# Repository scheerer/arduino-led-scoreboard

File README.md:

# Arduino LED Scoreboard

This project is intended to provide a simple arduino scoreboard based on the hub75 16x32 multi color LED (Example: [Adafruit - Medium 16x32 RGB LED matrix panel](https://www.adafruit.com/products/420)) and momentary RF receiver (Example: [Adafruit - Simple RF M4 315MHz](https://www.adafruit.com/products/1096))

# RF Receiver

Intended to be plugged directing into pins 2 thru 7 with the GND on pin 2

# LED Display

Wire as described in Adafruit's documentation for Arduino MEGA [LED Wiring Instructions](https://learn.adafruit.com/32x16-32x32-rgb-led-matrix/)

Feel free to ask questions...

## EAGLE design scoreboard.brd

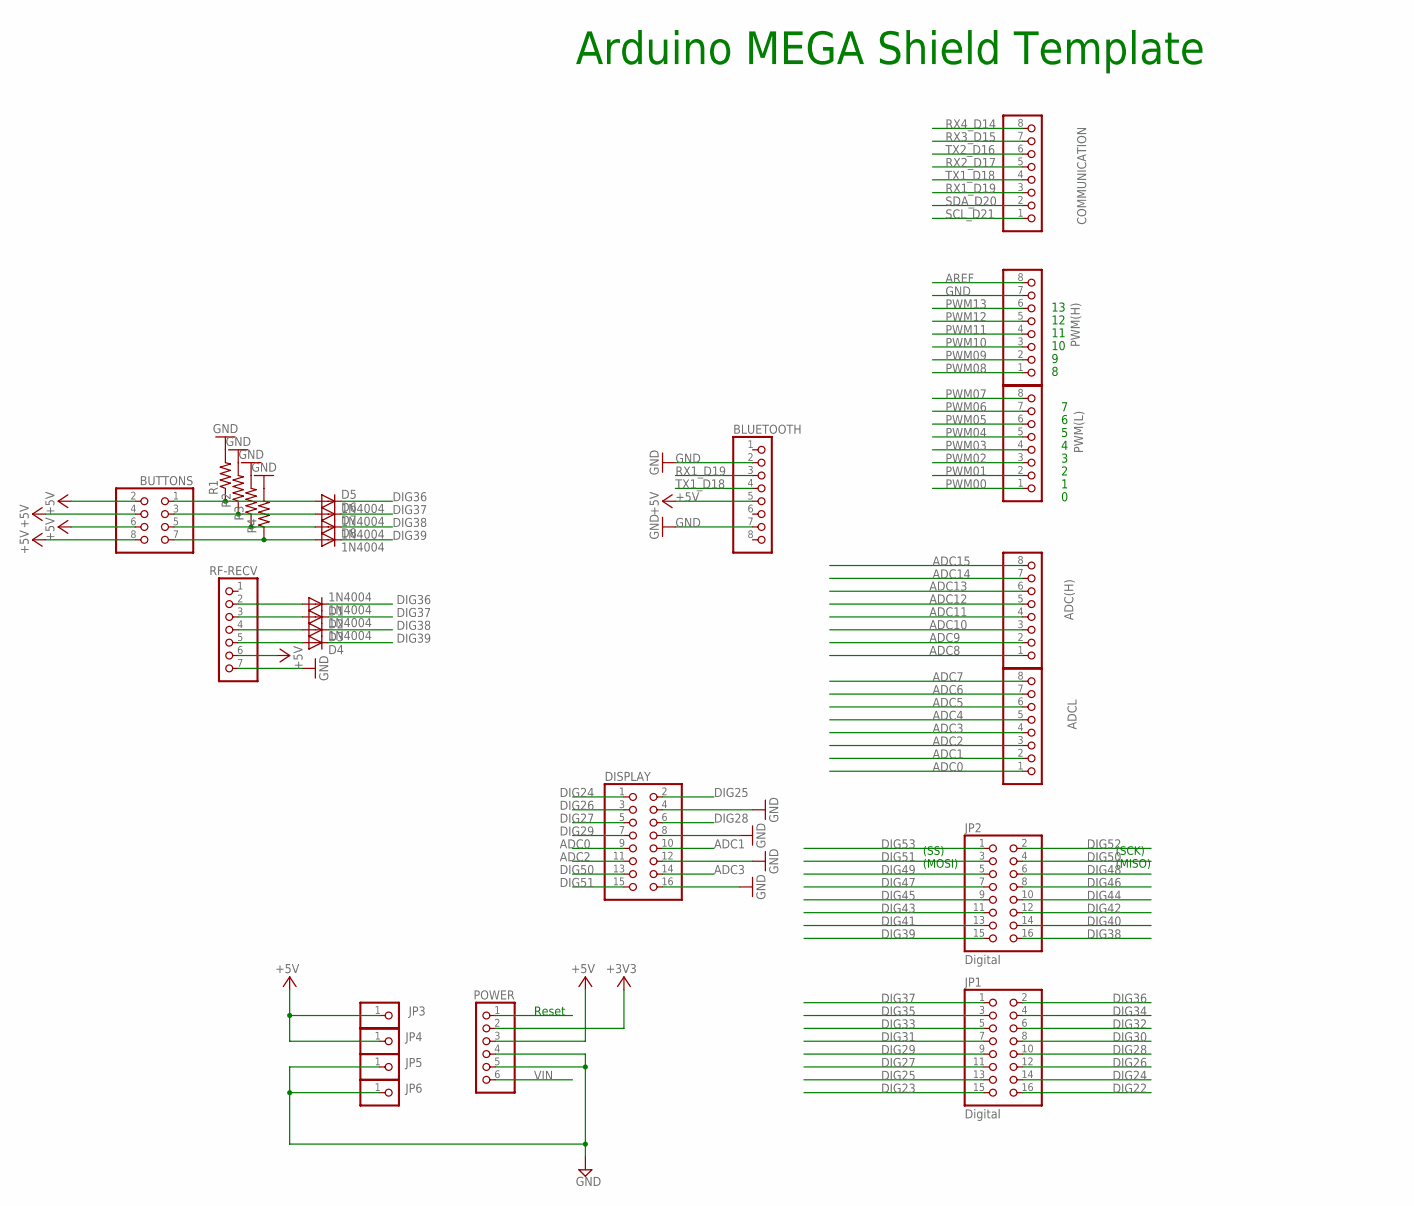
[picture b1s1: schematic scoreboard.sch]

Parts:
ADC(H): PINHD-1X8; 1X08
ADCL: PINHD-1X8; 1X08
BLUETOOTH: PINHD-1X8; 1X08
BUTTONS: PINHD-2X4; 2X04
COMMUNICATION: PINHD-1X8; 1X08
D1, D2, D3, D4, D5, D6, D7, D8: 1N4004; DO41-10
DISPLAY: PINHD-2X8; 2X08
JP1, JP2: Digital; 2X08
JP3, JP4, JP5, JP6: PINHD-1X1; 1X01
POWER: PINHD-1X6; 1X06
PWM(H): PINHD-1X8; 1X08
PWM(L): PINHD-1X8; 1X08
R1, R2, R3, R4: FLIPFLOP-RES; 0805-THM
RF-RECV: PINHD-1X7; 1X07

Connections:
+3V3: POWER.2
+5V: BLUETOOTH.5, BUTTONS.2, BUTTONS.4, BUTTONS.6, BUTTONS.8, JP3.1, JP4.1, POWER.3, RF-RECV.6
ADC0: ADCL.1, DISPLAY.9
ADC1: ADCL.2, DISPLAY.10
ADC2: ADCL.3, DISPLAY.11
ADC3: ADCL.4, DISPLAY.14
ADC4: ADCL.5
ADC5: ADCL.6
ADC6: ADCL.7
ADC7: ADCL.8
ADC8: ADC(H).1
ADC9: ADC(H).2
ADC10: ADC(H).3
ADC11: ADC(H).4
ADC12: ADC(H).5
ADC13: ADC(H).6
ADC14: ADC(H).7
ADC15: ADC(H).8
AREF: PWM(H).8
DIG22: JP1.16
DIG23: JP1.15
DIG24: DISPLAY.1, JP1.14
DIG25: DISPLAY.2, JP1.13
DIG26: DISPLAY.3, JP1.12
DIG27: DISPLAY.5, JP1.11
DIG28: DISPLAY.6, JP1.10
DIG29: DISPLAY.7, JP1.9
DIG30: JP1.8
DIG31: JP1.7
DIG32: JP1.6
DIG33: JP1.5
DIG34: JP1.4
DIG35: JP1.3
DIG36: D1.C, D5.C, JP1.2
DIG37: D2.C, D6.C, JP1.1
DIG38: D3.C, D7.C, JP2.16
DIG39: D4.C, D8.C, JP2.15
DIG40: JP2.14
DIG41: JP2.13
DIG42: JP2.12
DIG43: JP2.11
DIG44: JP2.10
DIG45: JP2.9
DIG46: JP2.8
DIG47: JP2.7
DIG48: JP2.6
DIG49: JP2.5
DIG50: DISPLAY.13, JP2.4
DIG51: DISPLAY.15, JP2.3
DIG52: JP2.2
DIG53: JP2.1
GND: BLUETOOTH.2, BLUETOOTH.7, DISPLAY.4, DISPLAY.8, DISPLAY.12, DISPLAY.16, JP5.1, JP6.1, POWER.4, POWER.5, PWM(H).7, R1.2, R2.2, R3.2, R4.2, RF-RECV.7
unnamed: D1.A, RF-RECV.2
unnamed: D2.A, RF-RECV.3
unnamed: D3.A, RF-RECV.4
unnamed: D4.A, RF-RECV.5
unnamed: BUTTONS.1, D5.A, R1.1
unnamed: BUTTONS.3, D6.A, R2.1
unnamed: BUTTONS.5, D7.A, R3.1
unnamed: BUTTONS.7, D8.A, R4.1
PWM00: PWM(L).1
PWM01: PWM(L).2
PWM02: PWM(L).3
PWM03: PWM(L).4
PWM04: PWM(L).5
PWM05: PWM(L).6
PWM06: PWM(L).7
PWM07: PWM(L).8
PWM08: PWM(H).1
PWM09: PWM(H).2
PWM10: PWM(H).3
PWM11: PWM(H).4
PWM12: PWM(H).5
PWM13: PWM(H).6
RESET: POWER.1
RX1_D19: BLUETOOTH.3, COMMUNICATION.3
RX2_D17: COMMUNICATION.5
RX3_D15: COMMUNICATION.7
RX4_D14: COMMUNICATION.8
SCL_D21: COMMUNICATION.1
SDA_D20: COMMUNICATION.2
TX1_D18: BLUETOOTH.4, COMMUNICATION.4
TX2_D16: COMMUNICATION.6
VIN: POWER.6

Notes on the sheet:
Arduino MEGA Shield Template
(SS)
(MOSI)
(SCK)
(MISO)
Reset

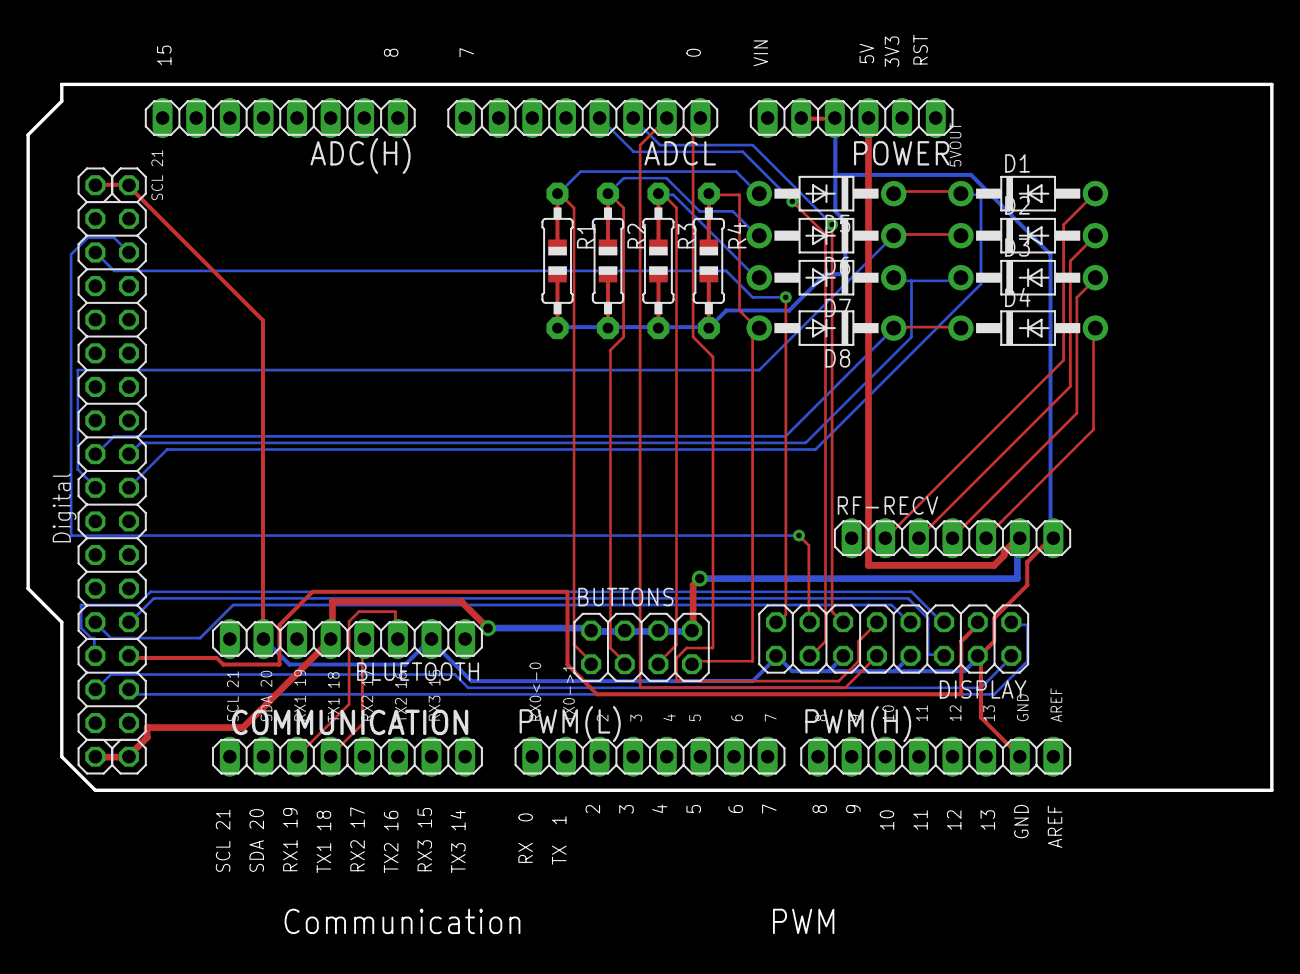
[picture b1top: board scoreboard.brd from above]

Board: 2 copper layers, 94.0 x 69.3 mm, 28 parts (0 on the bottom side), 28 nets.

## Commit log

2016-04-26 Initial thoughts
2016-04-28 Updates for real equipment
2016-04-28 Refactoring and better button control
2016-04-29 Draw flashing border for winner
2016-05-07 Adjust for Mega board
2016-05-10 Display Text
2016-05-11 Working with LAT on A4 now that I broke the A3 pin :(
2016-05-23 Blue/Green working with bigFont and RF receiver
2016-05-25 Common button library
2016-08-09 Updates from lastest user updates
2016-08-09 Add blank README
2016-08-09 Small doc updates
2016-08-09 Move schematics under own dir
2016-08-09 README updates
2016-08-09 Add License
